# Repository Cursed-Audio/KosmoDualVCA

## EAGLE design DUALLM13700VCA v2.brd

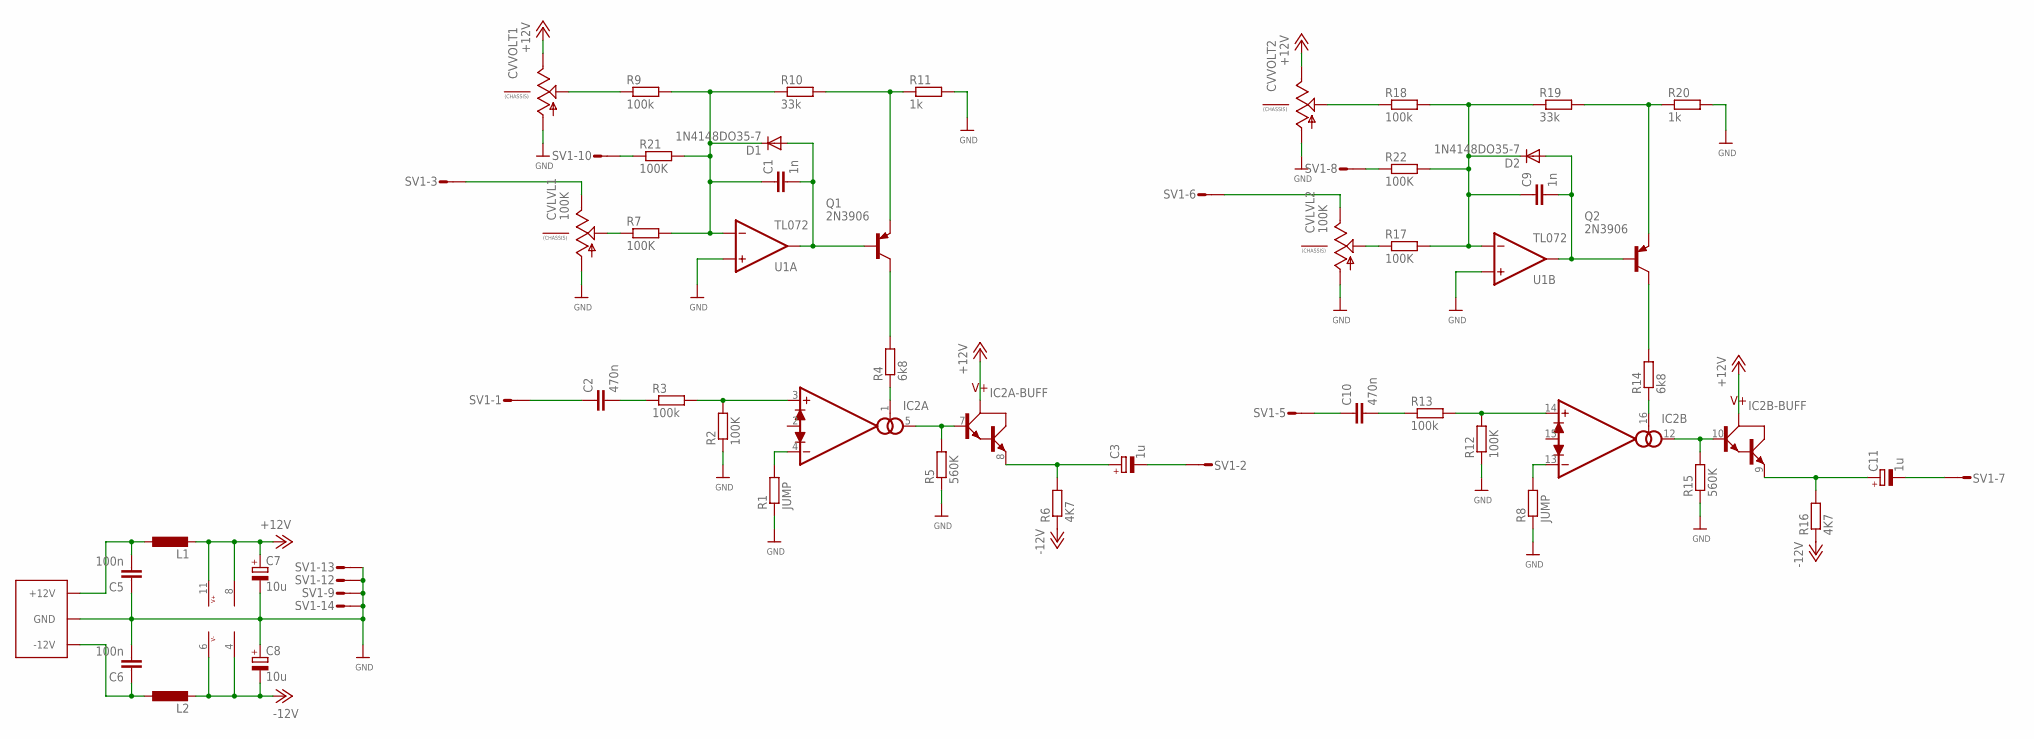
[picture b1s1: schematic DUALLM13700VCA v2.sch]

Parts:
C1, C9: 1n; C050-025X075
C2, C10: 470n; C050-025X075
C3, C11: 1u; E2-4
C4: EURO_POWER_LOCKSKINNY; EURO_POWER_HEADER
C5, C6: 100n; C050-025X075
C7, C8: 10u; E2-4
CVLVL1, CVLVL2: 100K; 9MM_SNAP-IN_POT
CVVOLT1, CVVOLT2: 9MM_SNAP-IN_POT_CHASSIS; 9MM_SNAP-IN_POT
D1, D2: 1N4148DO35-7; DO35-7
IC2: LM13700N; DIL16
L1, L2: L-EUIR-4; IR-4
Q1, Q2: 2N3906; TO92
R1, R8: JUMP; 0207/7
R2, R7, R12, R17, R21, R22: 100K; 0207/7
R3, R9, R13, R18: 100k; 0207/7
R4, R14: 6k8; 0207/7
R5, R15: 560K; 0207/7
R6, R16: 4K7; 0207/7
R10, R19: 33k; 0207/7
R11, R20: 1k; 0207/7
SV1: S14P
U1: TL072; DIL08-SML

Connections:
+12V: C7.+, CVVOLT1.3 (E), CVVOLT2.3 (E), IC2.11 (V+), L1.2, U1.8 (V+)
-12V: C8.-, IC2.6 (V-), L2.2, R6.1, R16.1, U1.4 (V-)
GND: C4.3 (GND), C4.4 (GND), C4.5 (GND), C4.6 (GND), C4.7 (GND), C4.8 (GND), C5.1, C6.2, C7.-, C8.+, CVLVL1.1 (A), CVLVL2.1 (A), CVVOLT1.1 (A), CVVOLT2.1 (A), R1.1, R2.1, R5.1, R8.1, R11.2, R12.1, R15.1, R20.2, SV1.9, SV1.12, SV1.13, SV1.14, U1.3 (+IN), U1.5 (+IN)
unnamed: IC2.3 (+IN), R2.2, R3.2
unnamed: IC2.4 (-IN), R1.2
unnamed: CVVOLT1.2 (S), R9.1
unnamed: C2.2, R3.1
unnamed: Q1.1 (C), R4.2
unnamed: IC2.1 (BIAS), R4.1
unnamed: C1.2, D1.A, Q1.2 (B), U1.1 (OUT)
unnamed: C1.1, D1.C, R7.2, R9.2, R10.1, R21.2, U1.2 (-IN)
unnamed: Q1.3 (E), R10.2, R11.1
unnamed: CVLVL1.2 (S), R7.1
unnamed: CVLVL1.3 (E), SV1.3
unnamed: IC2.5 (OUT), IC2.7 (IN), R5.2
unnamed: C4.9 (+12V), C4.10 (+12V), C5.2, L1.1
unnamed: C3.+, IC2.8 (OUT), R6.2
unnamed: C3.-, SV1.2
unnamed: C4.1 (-12V), C4.2 (-12V), C6.1, L2.1
unnamed: C2.1, SV1.1
unnamed: IC2.14 (+IN), R12.2, R13.2
unnamed: Q2.1 (C), R14.2
unnamed: IC2.16 (BIAS), R14.1
unnamed: C9.2, D2.A, Q2.2 (B), U1.7 (OUT)
unnamed: C9.1, D2.C, R17.2, R18.2, R19.1, R22.2, U1.6 (-IN)
unnamed: Q2.3 (E), R19.2, R20.1
unnamed: CVVOLT2.2 (S), R18.1
unnamed: CVLVL2.2 (S), R17.1
unnamed: CVLVL2.3 (E), SV1.6
unnamed: IC2.10 (IN), IC2.12 (OUT), R15.2
unnamed: C11.+, IC2.9 (OUT), R16.2
unnamed: C11.-, SV1.7
unnamed: IC2.13 (-IN), R8.2
unnamed: C10.2, R13.1
unnamed: C10.1, SV1.5
unnamed: R21.1, SV1.10
unnamed: R22.1, SV1.8

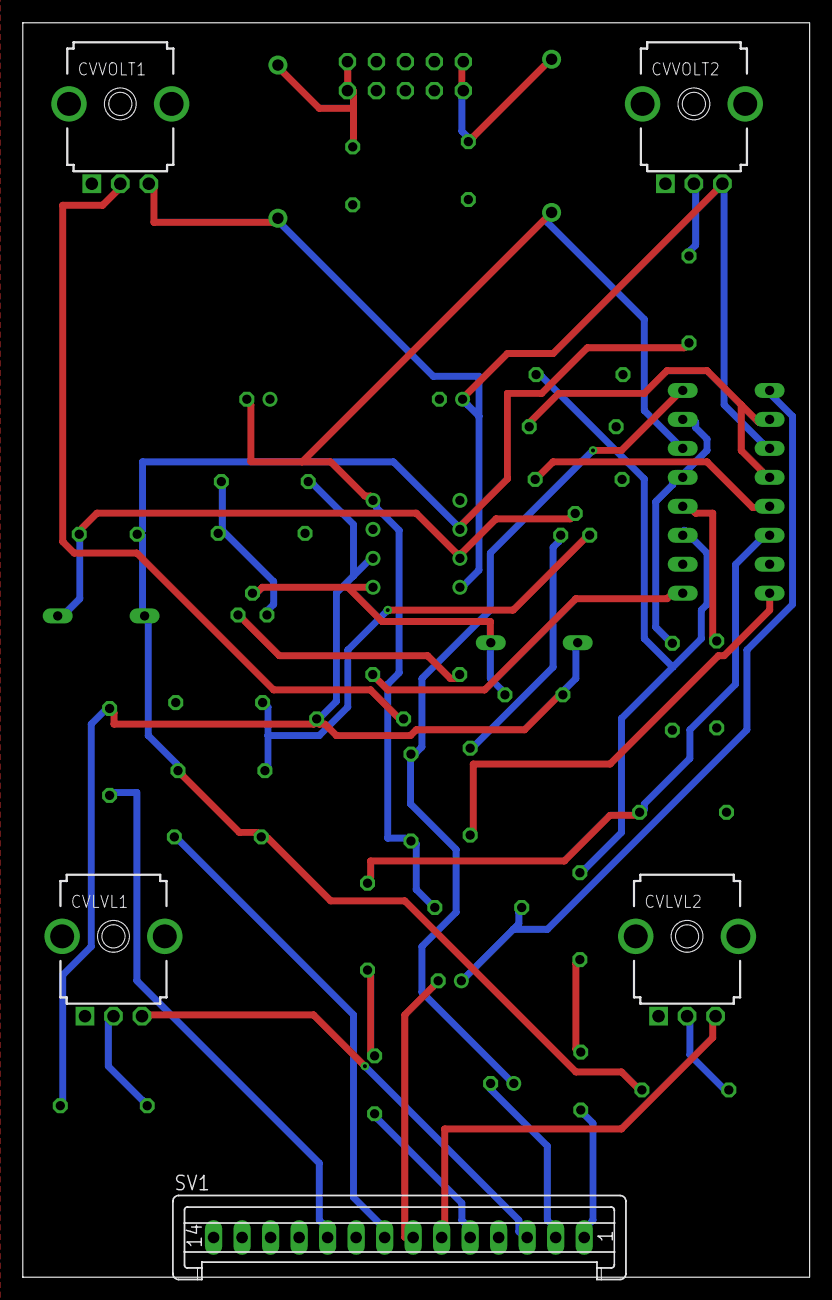
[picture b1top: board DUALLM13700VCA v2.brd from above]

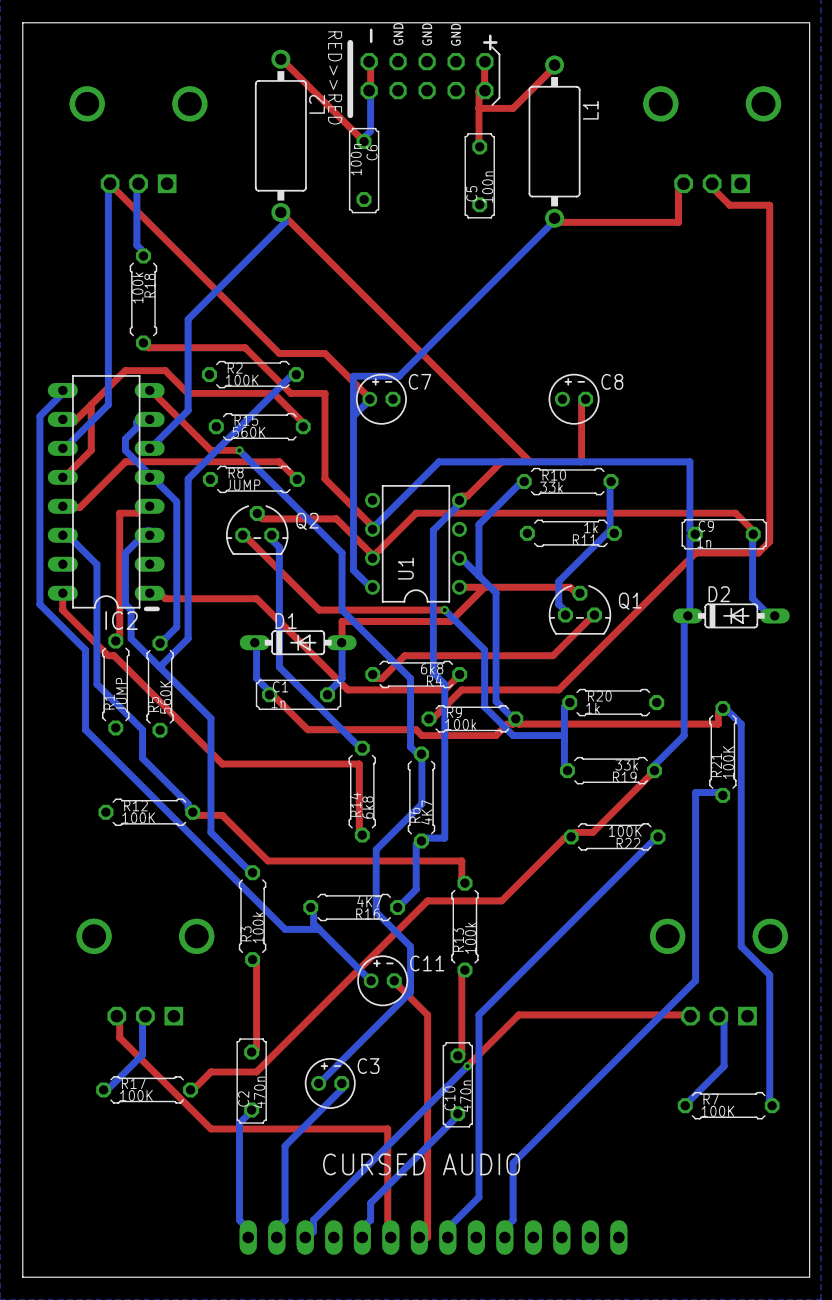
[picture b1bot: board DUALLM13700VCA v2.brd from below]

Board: 2 copper layers, 69.0 x 110.0 mm, 46 parts (41 on the bottom side), 37 nets.

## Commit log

2023-08-26 Add files via upload
    Ignore the gerber and eagle brd and sch files that are not V2 a small airwire error can be found in the CV section
